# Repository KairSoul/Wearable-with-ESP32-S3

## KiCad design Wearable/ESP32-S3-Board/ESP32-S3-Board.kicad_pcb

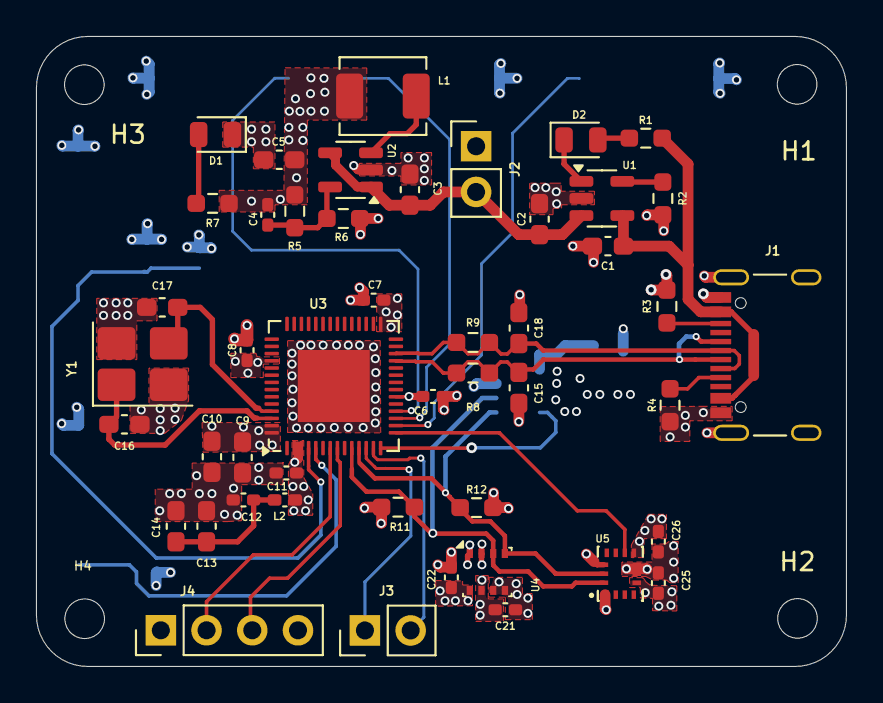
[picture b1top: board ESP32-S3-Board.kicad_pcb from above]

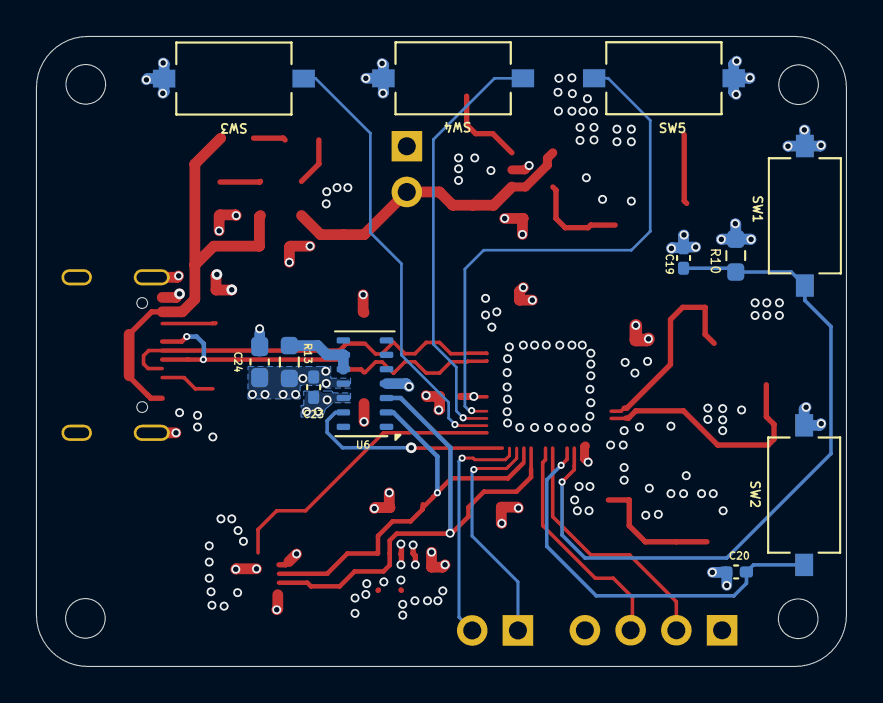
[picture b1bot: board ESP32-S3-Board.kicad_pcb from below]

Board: 4 copper layers, 45.0 x 35.0 mm, 63 parts (12 on the bottom side), 31 nets.

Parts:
C1, C2: 4.7u; C_0603_1608Metric_Pad1.08x0.95mm_HandSolder
C3, C5: 22u; C_0603_1608Metric_Pad1.08x0.95mm_HandSolder
C4: 22p; C_0402_1005Metric_Pad0.74x0.62mm_HandSolder
C6, C7, C8, C11, C12, C19, C20, C21, C22, C23, C25, C26: 100n; C_0402_1005Metric_Pad0.74x0.62mm_HandSolder
C9, C14, C24: 10u; C_0603_1608Metric_Pad1.08x0.95mm_HandSolder
C10, C13: 1u; C_0603_1608Metric_Pad1.08x0.95mm_HandSolder
C15, C18: NC; C_0603_1608Metric_Pad1.08x0.95mm_HandSolder
C16, C17: 10p; C_0603_1608Metric_Pad1.08x0.95mm_HandSolder
D1: G_LED; LED_0805_2012Metric
D2: R_LED; LED_0805_2012Metric
H1, H2, H3, H4: MountingHole; MountingHole_2.2mm_M2
J1: USB_C_Receptacle_USB2.0_16P; USB_C_Receptacle_Palconn_UTC16-G
J2, J3: Conn_01x02_Pin; PinHeader_1x02_P2.54mm_Vertical
J4: Conn_01x04_Pin; PinHeader_1x04_P2.54mm_Vertical
L1: 2.2u; L_Chilisin_BMRA00040420
L2: 2.0n; L_0402_1005Metric_Pad0.77x0.64mm_HandSolder
R1, R7: 470R; R_0603_1608Metric_Pad0.98x0.95mm_HandSolder
R2: 2k; R_0603_1608Metric_Pad0.98x0.95mm_HandSolder
R3, R4: 5.1k; R_0603_1608Metric_Pad0.98x0.95mm_HandSolder
R5: 100k; R_0603_1608Metric_Pad0.98x0.95mm_HandSolder
R6: 22k; R_0603_1608Metric_Pad0.98x0.95mm_HandSolder
R8, R9: 22R or 33R; R_0603_1608Metric_Pad0.98x0.95mm_HandSolder
R10: 10k; R_0603_1608Metric_Pad0.98x0.95mm_HandSolder
R11, R12: 4.7k; R_0603_1608Metric_Pad0.98x0.95mm_HandSolder
R13: 0R; R_0603_1608Metric_Pad0.98x0.95mm_HandSolder
SW1: BUTTON_EN; SW_Tactile_SPST_NO_Straight_CK_PTS636Sx25SMTRLFS
SW2: BUTTON_BOOTO; SW_Tactile_SPST_NO_Straight_CK_PTS636Sx25SMTRLFS
SW3: BUTTON1; SW_Tactile_SPST_NO_Straight_CK_PTS636Sx25SMTRLFS
SW4: BUTTON2; SW_Tactile_SPST_NO_Straight_CK_PTS636Sx25SMTRLFS
SW5: BUTTON3; SW_Tactile_SPST_NO_Straight_CK_PTS636Sx25SMTRLFS
U1: MCP73831-2-OT; SOT-23-5
U2: SY8089; SOT-23-5
U3: ESP32-S3; QFN-56-1EP_7x7mm_P0.4mm_EP4x4mm
U4: BME280; Bosch_LGA-8_2.5x2.5mm_P0.65mm_ClockwisePinNumbering
U5: BMI270; XDCR_BMI270
U6: MAX30102; Maxim_OLGA-14_3.3x5.6mm_P0.8mm
Y1: 3225; Crystal_SMD_3225-4Pin_3.2x2.5mm_HandSoldering

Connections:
/5V_VBUS: C1.1, J1.A4 (VBUS), J1.A9 (VBUS), J1.B4 (VBUS), J1.B9 (VBUS), R1.1, U1.4 (V_{DD})
/MCU_ESP32-S3/BOOTO: C20.1, SW2.2, U3.5 (GPIO0)
/MCU_ESP32-S3/BUTTON1: SW3.1, U3.16 (GPIO11)
/MCU_ESP32-S3/BUTTON2: SW4.1, U3.17 (GPIO12)
/MCU_ESP32-S3/BUTTON3: SW5.1, U3.18 (GPIO13)
/MCU_ESP32-S3/EN: C19.1, R10.2, SW1.2, U3.4 (CHIP_PU)
/MCU_ESP32-S3/INT2_BMI: U3.15 (GPIO10), U5.9 (INT2)
/MCU_ESP32-S3/INT_MAX: U3.14 (GPIO9), U6.13 (~INT)
/MCU_ESP32-S3/RXD: J3.1, U3.12 (GPIO7)
/MCU_ESP32-S3/SCL: R12.2, U3.11 (GPIO6), U4.4 (SCK), U5.13 (SCX), U6.2 (SCL)
/MCU_ESP32-S3/SCL_OLED: J4.3, U3.8 (GPIO3)
/MCU_ESP32-S3/SDA: R11.2, U3.10 (GPIO5), U4.3 (SDI), U5.14 (SDX), U6.3 (SDA)
/MCU_ESP32-S3/SDA_OLED: J4.2, U3.7 (GPIO2)
/MCU_ESP32-S3/TXD: J3.2, U3.13 (GPIO8)
/MCU_ESP32-S3/XTAL_N: C17.1, U3.53 (XTAL_N), Y1.3
/MCU_ESP32-S3/XTAL_P: C16.2, U3.54 (XTAL_P), Y1.1
/USB_D+: C18.2, J1.A7 (D-), J1.B7 (D-), R9.1, R9.2, U3.26 (GPIO20/USB_D+)
/USB_D-: C15.1, J1.A6 (D+), J1.B6 (D+), R8.1, R8.2, U3.25 (GPIO19/USB_D-)
/VDD33: C4.1, C5.1, C6.1, C7.1, C8.1, C9.1, C10.1, C11.1, C21.1, C22.1, C23.1, C24.1, C25.1, C26.1, J4.4, L1.2, L2.1, R5.1, R7.1, R10.1, R11.1, R12.1, R13.2, U3.2 (VDD3P3), U3.3 (VDD3P3), U3.20 (VDD3P3_RTC), U3.29 (VDD_SPI), U3.46 (VDD3P3_CPU), U3.55 (VDDA), U3.56 (VDDA), U4.2 (CSB), U4.5 (SDO), U4.6 (VDDIO), U4.8 (VDD), U5.1 (SDO), U5.5 (VDDIO), U5.8 (VDD), U5.12 (CSB), U6.11 (VDD)
GND: C1.2, C2.2, C3.2, C5.2, C6.2, C7.2, C8.2, C9.2, C10.2, C11.2, C12.2, C13.2, C14.2, C15.2, C16.1, C17.2, C18.1, C19.2, C20.2, C21.2, C22.2, C23.2, C24.2, C25.2, C26.2, D1.1 (K), J1.A1 (GND), J1.B1 (GND), J1.S1 (SHIELD), J2.1, J4.1, R2.1, R3.2, R4.2, R6.2, SW1.1, SW2.1, SW3.2, SW4.2, SW5.2, U1.2 (V_{SS}), U2.2 (GND), U3.57 (GND), U4.1 (GND), U4.7 (GND), U5.6 (GNDIO), U5.7 (GND), U6.4 (PGND), U6.12 (GND), Y1.2, Y1.4
unnamed: C12.1, C13.1, C14.1, L2.2
unnamed: D1.2 (A), R7.2
unnamed: D2.2 (A), R1.2
unnamed: D2.1 (K), U1.1 (STAT)
unnamed: J1.A5 (CC1), R4.1
unnamed: J1.B5 (CC2), R3.1
unnamed: R13.1, U6.9 (VLED+), U6.10 (VLED+)
unnamed: R2.2, U1.5 (PROG)
unnamed: C4.2, R5.2, R6.1, U2.5 (FB)
unnamed: L1.1, U2.3 (LX)
V_BAT: C2.1, C3.1, J2.2, U1.3 (V_{BAT}), U2.1 (EN), U2.4 (IN)
